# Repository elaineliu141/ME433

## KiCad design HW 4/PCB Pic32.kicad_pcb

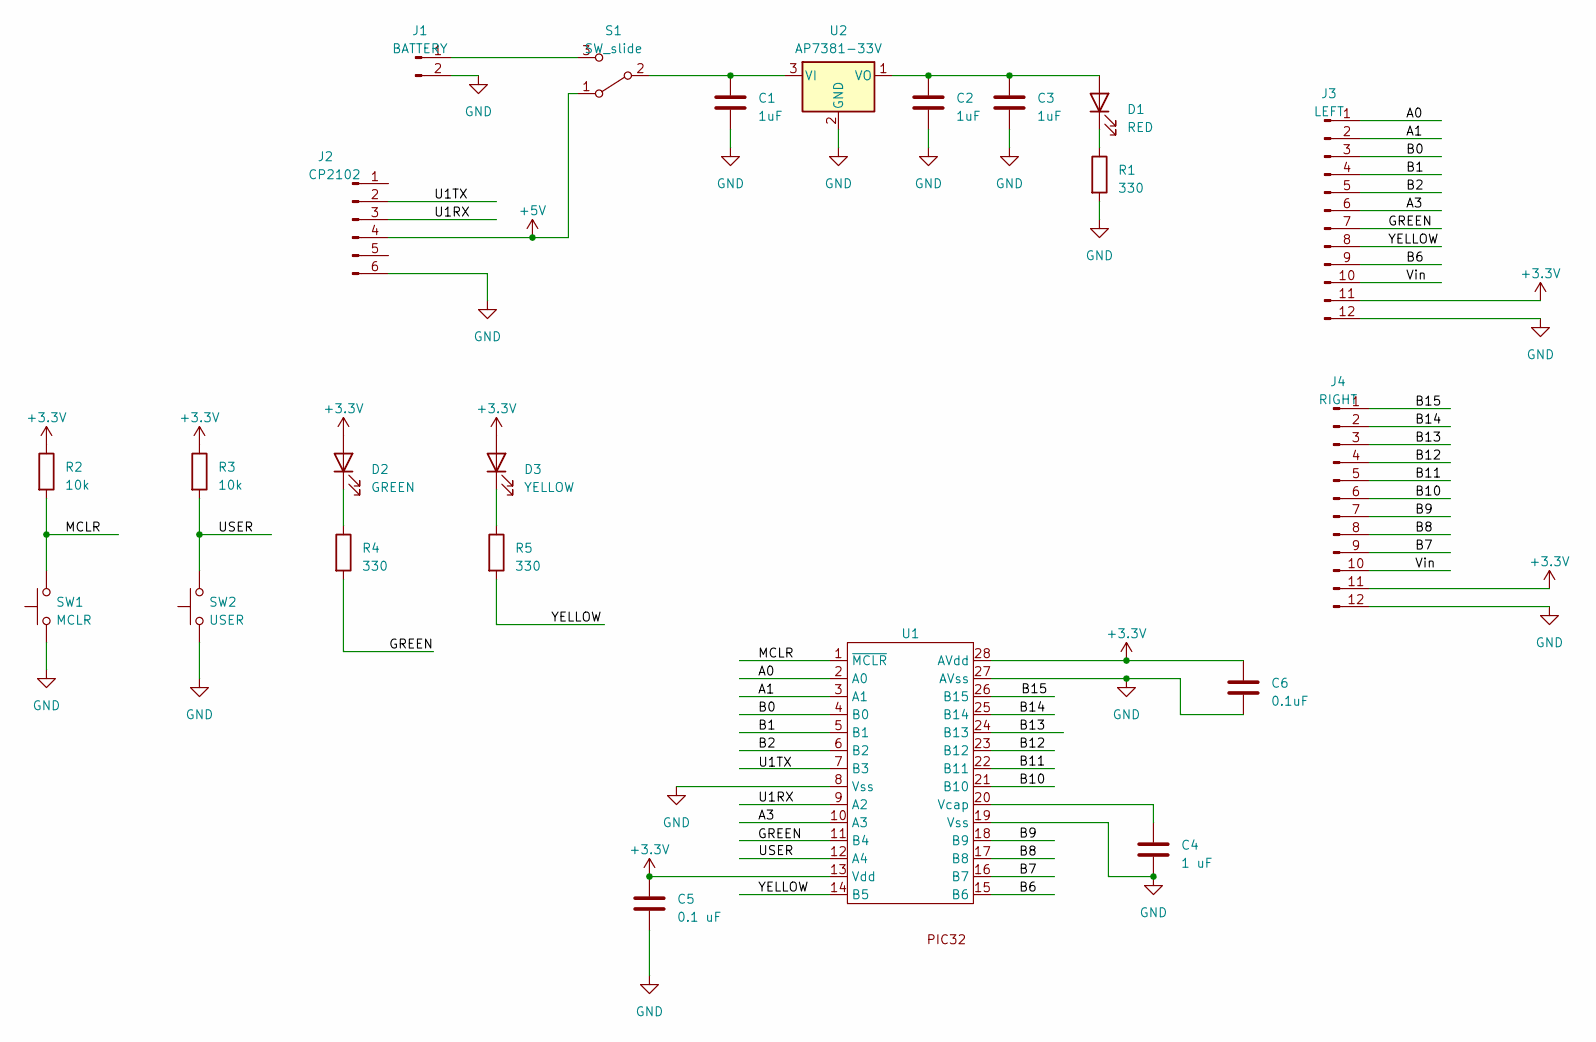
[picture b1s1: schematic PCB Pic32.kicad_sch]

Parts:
C1, C2, C3: 1uF; C_Disc_D5.1mm_W3.2mm_P5.00mm
C4: 1 uF; C_Disc_D5.1mm_W3.2mm_P5.00mm
C5: 0.1 uF; C_Disc_D3.4mm_W2.1mm_P2.50mm
C6: 0.1uF; C_Disc_D3.4mm_W2.1mm_P2.50mm
D1: RED; LED_D3.0mm
D2: GREEN; LED_D3.0mm
D3: YELLOW; LED_D3.0mm
J1: BATTERY; PinSocket_1x02_P2.54mm_Vertical
J2: CP2102; PinSocket_1x06_P2.54mm_Vertical
J3: LEFT; PinSocket_1x12_P2.54mm_Vertical
J4: RIGHT; PinSocket_1x12_P2.54mm_Vertical
R1, R4, R5: 330; R_Axial_DIN0207_L6.3mm_D2.5mm_P7.62mm_Horizontal
R2, R3: 10k; R_Axial_DIN0207_L6.3mm_D2.5mm_P7.62mm_Horizontal
S1: SW_slide; slide
SW1: MCLR; pushb
SW2: USER; pushb
U1: DIP-28_W7.62mm_Socket
U2: AP7381-33V; TO-92L_Inline

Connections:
+3.3V: C5.1, C6.1, D2.2 (A), D3.2 (A), J3.11, J4.11, R2.1, R3.1, U1.13 (Vdd), U1.28 (AVdd)
+5V: J2.4, S1.1 (A)
/A0: J3.1, U1.2 (A0)
/A1: J3.2, U1.3 (A1)
/A3: J3.6, U1.10 (A3)
/B0: J3.3, U1.4 (B0)
/B1: J3.4, U1.5 (B1)
/B2: J3.5, U1.6 (B2)
/B6: J3.9, U1.15 (B6)
/B7: J4.9, U1.16 (B7)
/B8: J4.8, U1.17 (B8)
/B9: J4.7, U1.18 (B9)
/B10: J4.6, U1.21 (B10)
/B11: J4.5, U1.22 (B11)
/B12: J4.4, U1.23 (B12)
/B13: J4.3, U1.24 (B13)
/B14: J4.2, U1.25 (B14)
/B15: J4.1
/GREEN: J3.7, R4.2
/MCLR: R2.2, SW1.2, U1.1 (~MCLR)
/U1RX: J2.3, U1.9 (A2)
/U1TX: J2.2
/USER: R3.2, SW2.2
/Vin: J3.10, J4.10
/YELLOW: J3.8, R5.2, U1.14 (B5)
GND: C1.2, C2.2, C3.2, C4.2, C5.2, C6.2, J1.2, J2.6, J3.12, J4.12, R1.2, SW1.1, SW2.1, U1.8 (Vss), U1.19 (Vss), U1.27 (AVss), U2.2 (GND)
unnamed: C2.1, C3.1, D1.2 (A), U2.1 (VO)
unnamed: D1.1 (K), R1.1
unnamed: D2.1 (K), R4.1
unnamed: D3.1 (K), R5.1
unnamed: J1.1, S1.3 (C)
unnamed: C1.1, S1.2 (B), U2.3 (VI)
unnamed: C4.1, U1.20 (Vcap)

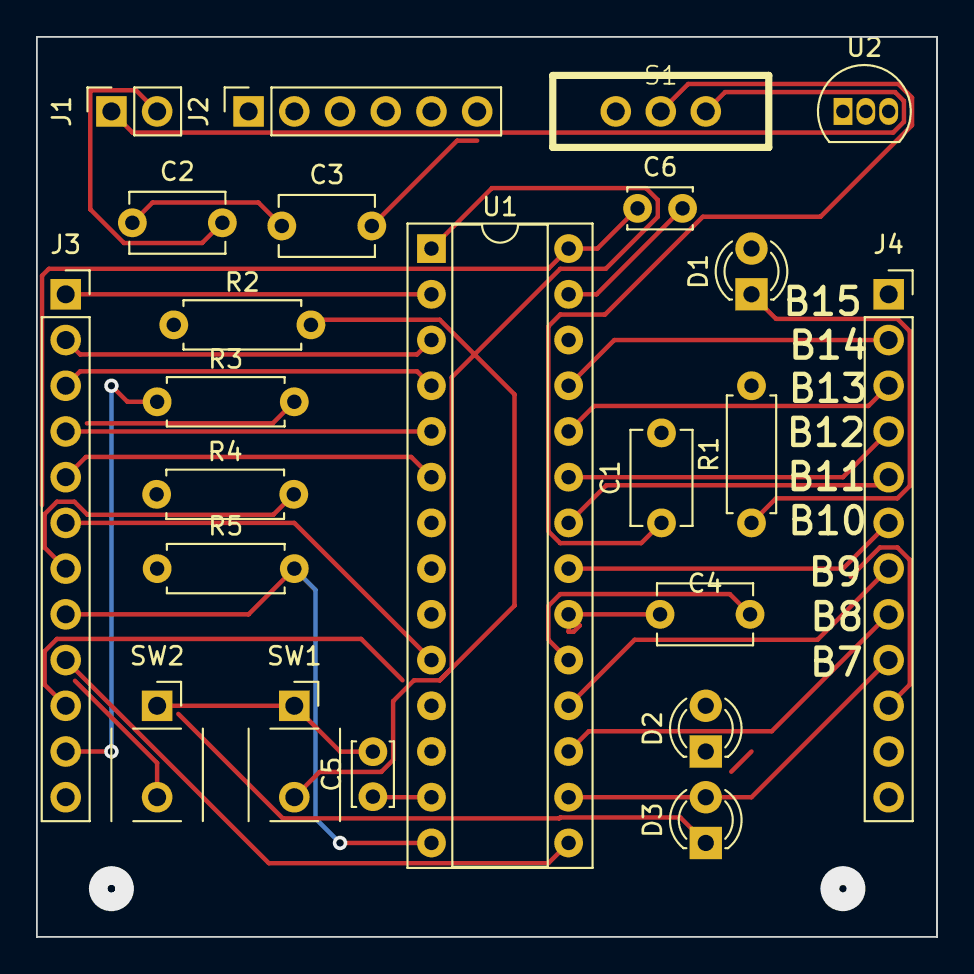
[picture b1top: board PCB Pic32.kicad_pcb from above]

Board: 2 copper layers, 50.0 x 50.0 mm, 23 parts (0 on the bottom side), 31 nets.

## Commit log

2023-04-04 uploaded code
2023-04-05 python plotter w code
2023-04-08 uploaded schematic diagram and kicad files
2023-04-12 added board layout
2023-04-13 added hw5
2023-04-18 sin and tri waves
2023-04-18 changed
2023-04-22 hw 7
2023-04-27 hw 8
2023-04-27 movie
2023-05-03 filter code
2023-05-09 neopixel
2023-05-10 pico plot
2023-05-23 added pico website
2023-05-24 project
2023-05-24 servo motor
2023-06-02 camera sensing
2023-06-02 robot
